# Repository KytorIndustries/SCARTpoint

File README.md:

# SCARTpoint
Connect an RGBs (Red, Green, Blue, CSync) signal over SCART to an Extron Crosspoint. 

The SCARTpoint adapter allows a direct SCART connection to the Extron CrossPoint matrix switch. There are two geometries, an "upper" (3E-300009) and a "lower" (3E-300010), they need to be installed in an alternating pattern, two of the same geometry cannot be installed adjacently. Both geometries are configurable as inputs (to Extron) or outputs (from Extron) using solder jumpers and the proper components.

This is for use only with Extron Crosspoint matrix switches with the following BNC center-to-center dimensions:
- Horizontal: 	17.2 mm
- Vertical:		16.5 mm
- This will not fit older units with 20.3 mm vertical distance.

Fully assembled and QC tested SCARTpoint adapters can be [purchased here](https://kytor.com/store/product/scartpoint/).

## Files Included
- **PCB Design Files** (KiCAD, Gerber)
- **Bill of Materials** (XLSX)
- **CAD** (STEP)
- **Photos**

## Features
- SCART-Lock mounting posts in accordance with [KTL 0158](https://github.com/KytorIndustries/scart-mounting/blob/main/KTL_0158.pdf) specification.
- Female SCART connection.
- Female TRS 3.5mm stereo audio connection.
- Male RCA Red, Green, Blue, Sync connections.
- Input Only: LM1881M Sync Stripper for CSync. (Optional)
- Input Only: Switch to Disable or Enable Sync Stripper. (Optional)
- Output Only: 470 ohm Resistor for 75ohm level CSync.

## Additional Parts Required
- [SCART-Lock](https://kytor.com/store/product/rt4k-scart-lock/) or [Print Your Own](https://www.printables.com/model/873880)
- [90 Degree Stereo TRS Cable](https://amzn.to/44nj7Mh)
- [BNC Male to RCA Male Adapter](https://www.aliexpress.us/item/3256803887270180.html) (4x)
- [Phoenix to 3.5 mm Adapter](https://github.com/arithmaldor/phoenix-audio-adapter-kicad)

## Assembly
1. Input Only: Solder C1, C2, U1 and SW1 in place. Alternatively if sync stripper is not needed, C1, C2, U1 and SW1 may be left unpopulated and jumper JP4 can be soldered.
2. Output Only: Solder R1 in place.
3. Both: Solder J4-6 in place. P1-2 may be soldered in place as mounting posts for the SCART-Lock.
2. Close solder jumpers JP1-3 appropriately for either input or output type.

## PCB Revision History
- Rev 0 - Initial production release

## Resources and Credits
This project was inspired by the [rattboi adapters](https://github.com/rattboi/extron-scart-adapter).

## License
This project is open-source under the [CC BY 4.0 (Attribution 4.0 International)](https://creativecommons.org/licenses/by/4.0/).

## Disclaimer
This project is provided "as-is" without any warranty, express or implied, including but not limited to warranties of merchantability or fitness for a particular purpose. No support is provided.

Amazon links are affiliates.

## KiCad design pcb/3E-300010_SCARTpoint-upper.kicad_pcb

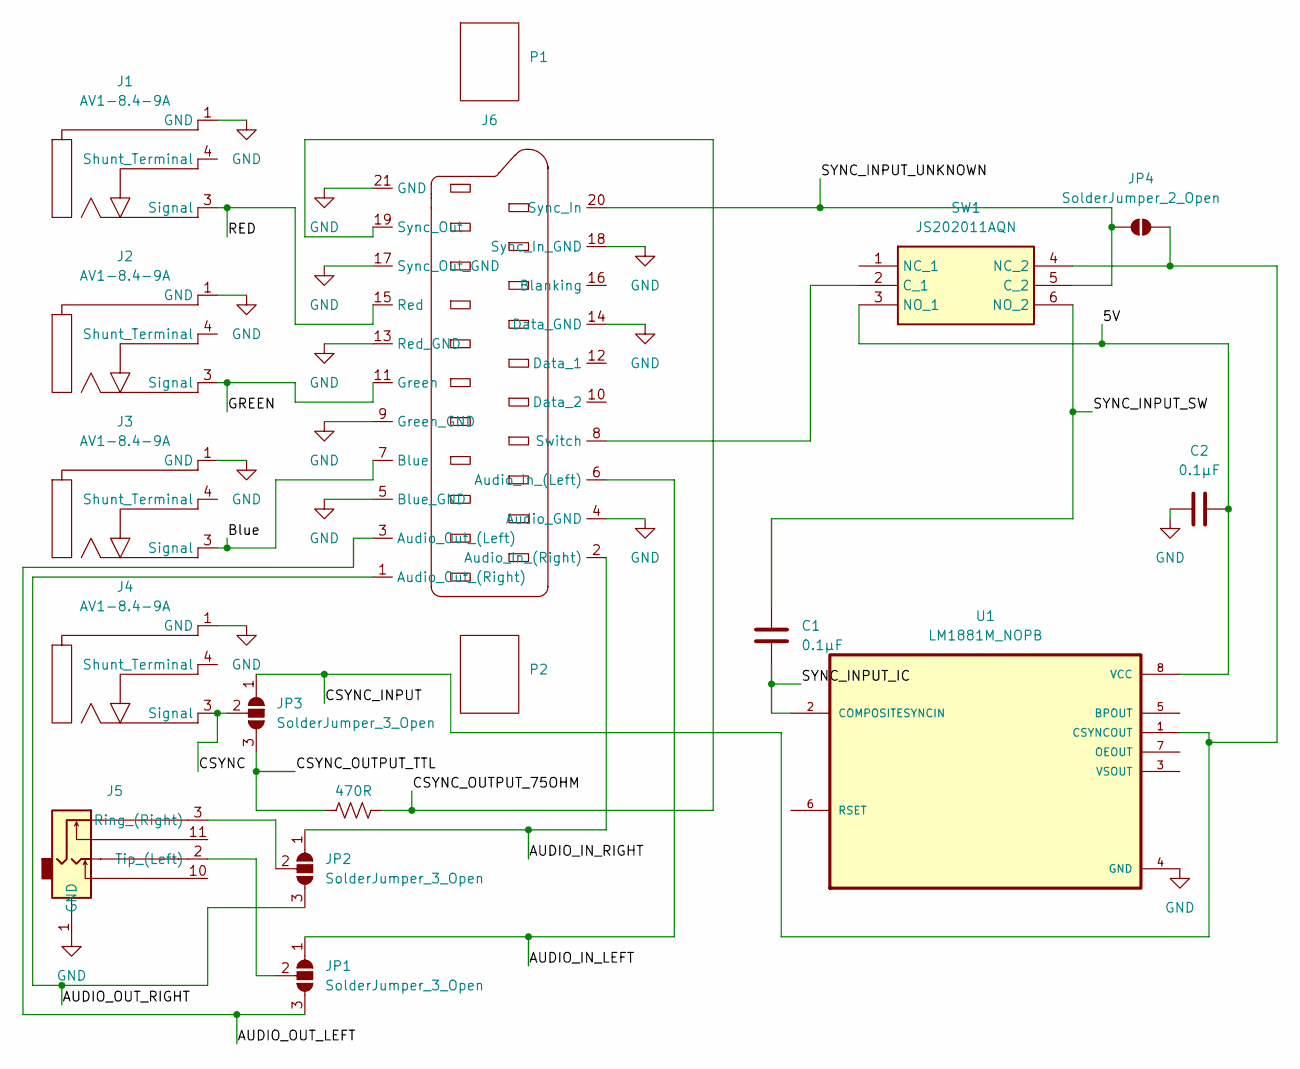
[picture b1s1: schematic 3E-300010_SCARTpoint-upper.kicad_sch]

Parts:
C1, C2: 0.1µF; C_0805_2012Metric_Pad1.18x1.45mm_HandSolder
J1, J2, J3, J4: AV1-8.4-9A; 1-RCA 972 (AV1-8.4-91)
J5: Female_Stereo_3.5mm_SJ1-3525N
J6: Female_SCART_(90)
JP1, JP2, JP3: SolderJumper_3_Open; Solder Jumper Small 3-Way
JP4: SolderJumper_2_Open; Jumper Small (1.5x1mm)
P1, P2: PEM M4 Post SMTRAM4-9-7ET
R1: 470R; R_0805_2012Metric_Pad1.20x1.40mm_HandSolder
SW1: JS202011AQN; Mouser Part Number 611-JS202011AQN
U1: LM1881M_NOPB; LM1881M

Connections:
/5V: C2.2, SW1.3 (NO_1), U1.8 (VCC)
/AUDIO_IN_LEFT: J6.6 (Audio_In_(Left)), JP1.1 (A)
/AUDIO_IN_RIGHT: J6.2 (Audio_In_(Right)), JP2.1 (A)
/AUDIO_OUT_LEFT: J6.3 (Audio_Out_(Left)), JP1.3 (B)
/AUDIO_OUT_RIGHT: J6.1 (Audio_Out_(Right)), JP2.3 (B)
/Blue: J3.3 (Signal), J6.7 (Blue)
/CSYNC: J4.3 (Signal), JP3.2 (C)
/CSYNC_INPUT: JP3.1 (A), JP4.2 (B), SW1.4 (NC_2), U1.1 (CSYNCOUT)
/CSYNC_OUTPUT_75OHM: J6.19 (Sync_Out), R1.2
/CSYNC_OUTPUT_TTL: JP3.3 (B), R1.1
/GREEN: J2.3 (Signal), J6.11 (Green)
/RED: J1.3 (Signal), J6.15 (Red)
/SYNC_INPUT_IC: C1.2, U1.2 (COMPOSITESYNCIN)
/SYNC_INPUT_SW: C1.1, SW1.6 (NO_2)
/SYNC_INPUT_UNKNOWN: J6.20 (Sync_In), JP4.1 (A), SW1.5 (C_2)
GND: C2.1, J1.1 (GND), J2.1 (GND), J3.1 (GND), J4.1 (GND), J5.1 (GND), J6.4 (Audio_GND), J6.5 (Blue_GND), J6.9 (Green_GND), J6.13 (Red_GND), J6.14 (Data_GND), J6.17 (Sync_Out_GND), J6.18 (Sync_In_GND), J6.21 (GND), U1.4 (GND)
unnamed: J5.3 (Ring_(Right)), JP2.2 (C)
unnamed: J5.2 (Tip_(Left)), JP1.2 (C)
unnamed: J6.8 (Switch), SW1.2 (C_1)

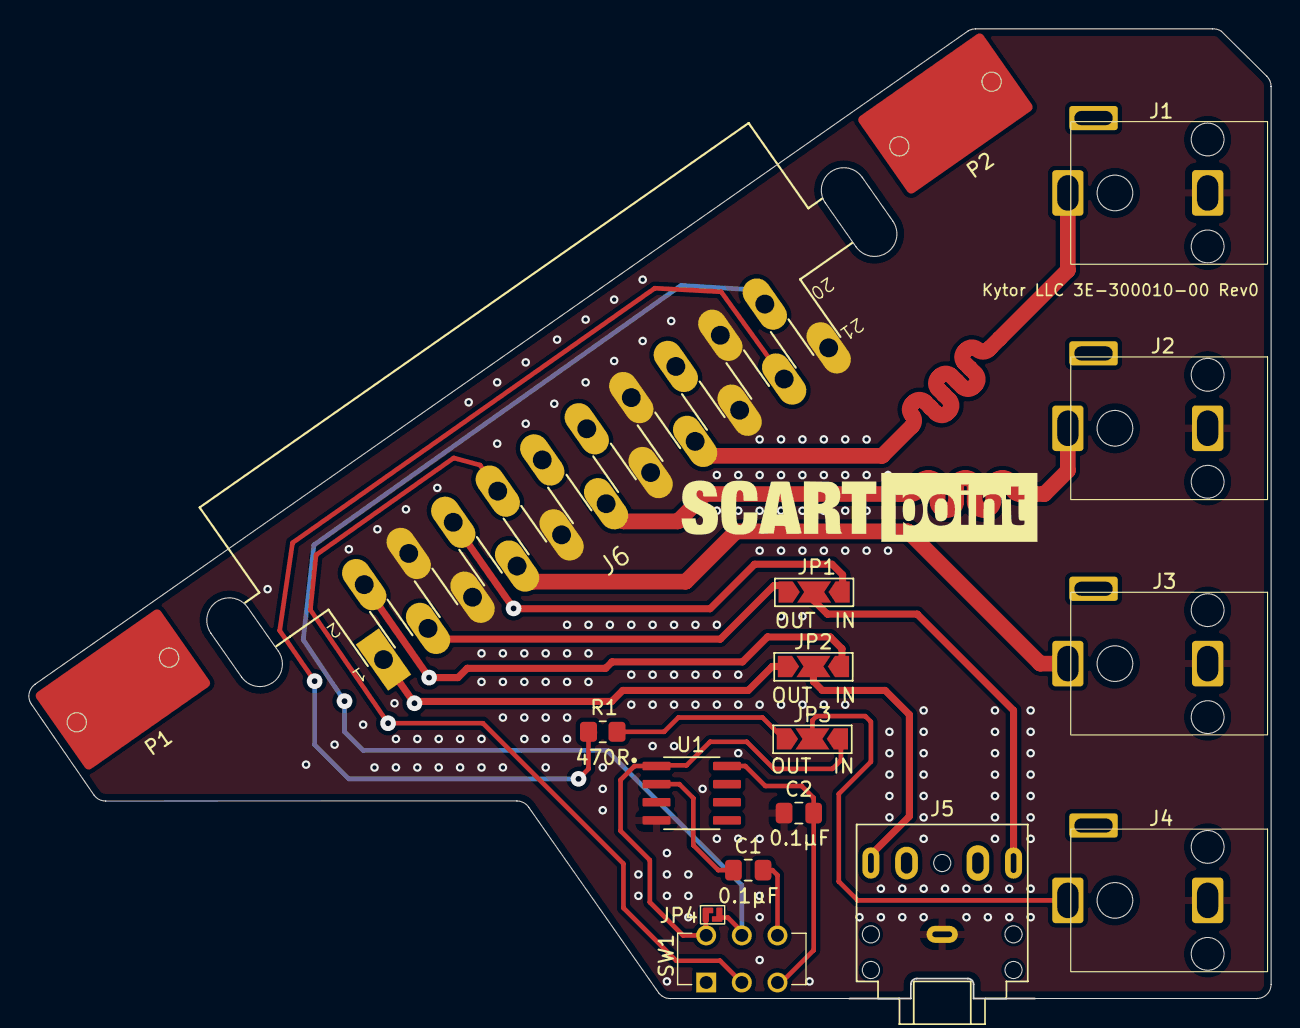
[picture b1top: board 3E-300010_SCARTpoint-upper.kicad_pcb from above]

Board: 2 copper layers, 87.0 x 67.9 mm, 17 parts (0 on the bottom side), 19 nets.

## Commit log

2025-05-21 Initial Upload
